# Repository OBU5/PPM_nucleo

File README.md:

# Proton precession magnetometer

Official repository for Proton precession magnetometer
In this repository are HW and SW files for the diploma thesis that is about designing, constrocting of proton precession magnetometer and analysis of its signal.
The aim is to construct PPM device that will be used for the earth’s magnetic field measurement

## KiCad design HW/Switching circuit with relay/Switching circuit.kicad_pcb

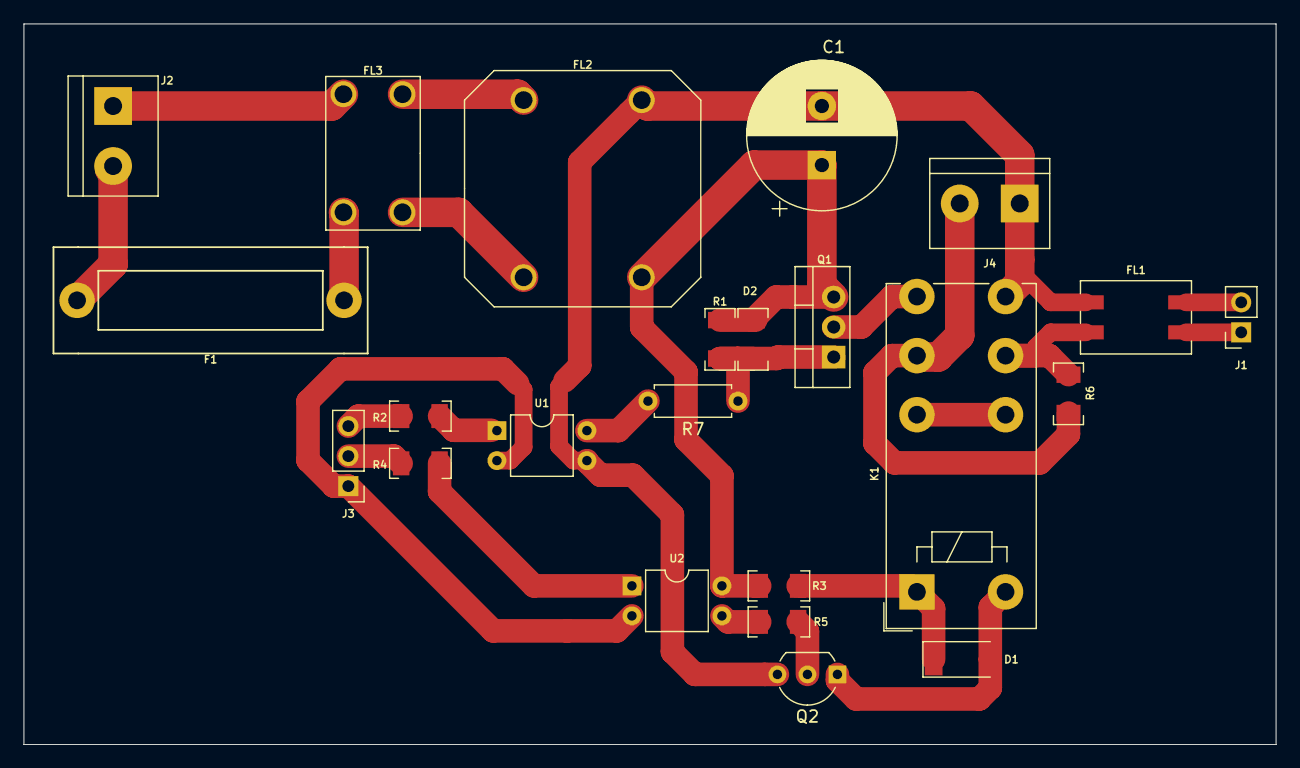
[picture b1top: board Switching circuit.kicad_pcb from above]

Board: 2 copper layers, 106.0 x 61.0 mm, 23 parts (0 on the bottom side), 24 nets.

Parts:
C1: CP; CP_Radial_D12.5mm_P5.00mm
D1: D; D_MELF
D2: 15V; R1206
F1: Fuse; Fuse_Holder-PTF15
FL1: Filter; WE-SL2
FL2: Filter; Choke1
FL3: Filter; Choke2
J1: Signal; PinSocket_1x02_P2.54mm_Vertical
J2: Power; TerminalBlock_2pin_Pitch5.08mm
J3: MCU; PinHeader_1x03_P2.54mm_Vertical
J4: PPM_sensor; TerminalBlock_2pin_Pitch5.08mm
K1: FINDER-41.52; Relay_DPDT_Finder_40.52
Q1: IRF9640; TO-220-3_Vertical
Q2: BC547; TO-92_Inline_Wide
R1: 2k2; R1206
R2, R4: 470; R1206
R3: 0; R1206
R5: 4k7; R1206
R6: 10k; R1206
R7: 1k; R_Axial_DIN0207_L6.3mm_D2.5mm_P7.62mm_Horizontal
U1, U2: LTV-817; DIP-4_W7.62mm

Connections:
+12V: C1.1, D2.1, FL2.3, Q1.3, R1.1, R3.1, U2.4
FET: J3.3, R2.2
GNDA: C1.2, FL1.1, FL2.4, J4.1, K1.24, Q2.3, U1.3
GNDD: J3.1, U1.2, U2.2
unnamed: D1.1, K1.A1, R3.2
unnamed: D1.2, K1.A2, Q2.1
unnamed: D2.2, Q1.1, R1.2, R7.1
unnamed: F1.1, FL3.2
unnamed: F1.2, J2.2
unnamed: FL1.3, J1.1
unnamed: FL1.4, J1.2
unnamed: FL2.1, FL3.4
unnamed: FL2.2, FL3.3
unnamed: FL3.1, J2.1
unnamed: J4.2, K1.11, R6.2
unnamed: K1.12, K1.22
unnamed: K1.14, Q1.2
unnamed: Q2.2, R5.2
unnamed: R2.1, U1.1
unnamed: R4.1, U2.1
unnamed: R5.1, U2.3
unnamed: R7.2, U1.4
Relay: J3.2, R4.2
Sig_out: FL1.2, K1.21, R6.1

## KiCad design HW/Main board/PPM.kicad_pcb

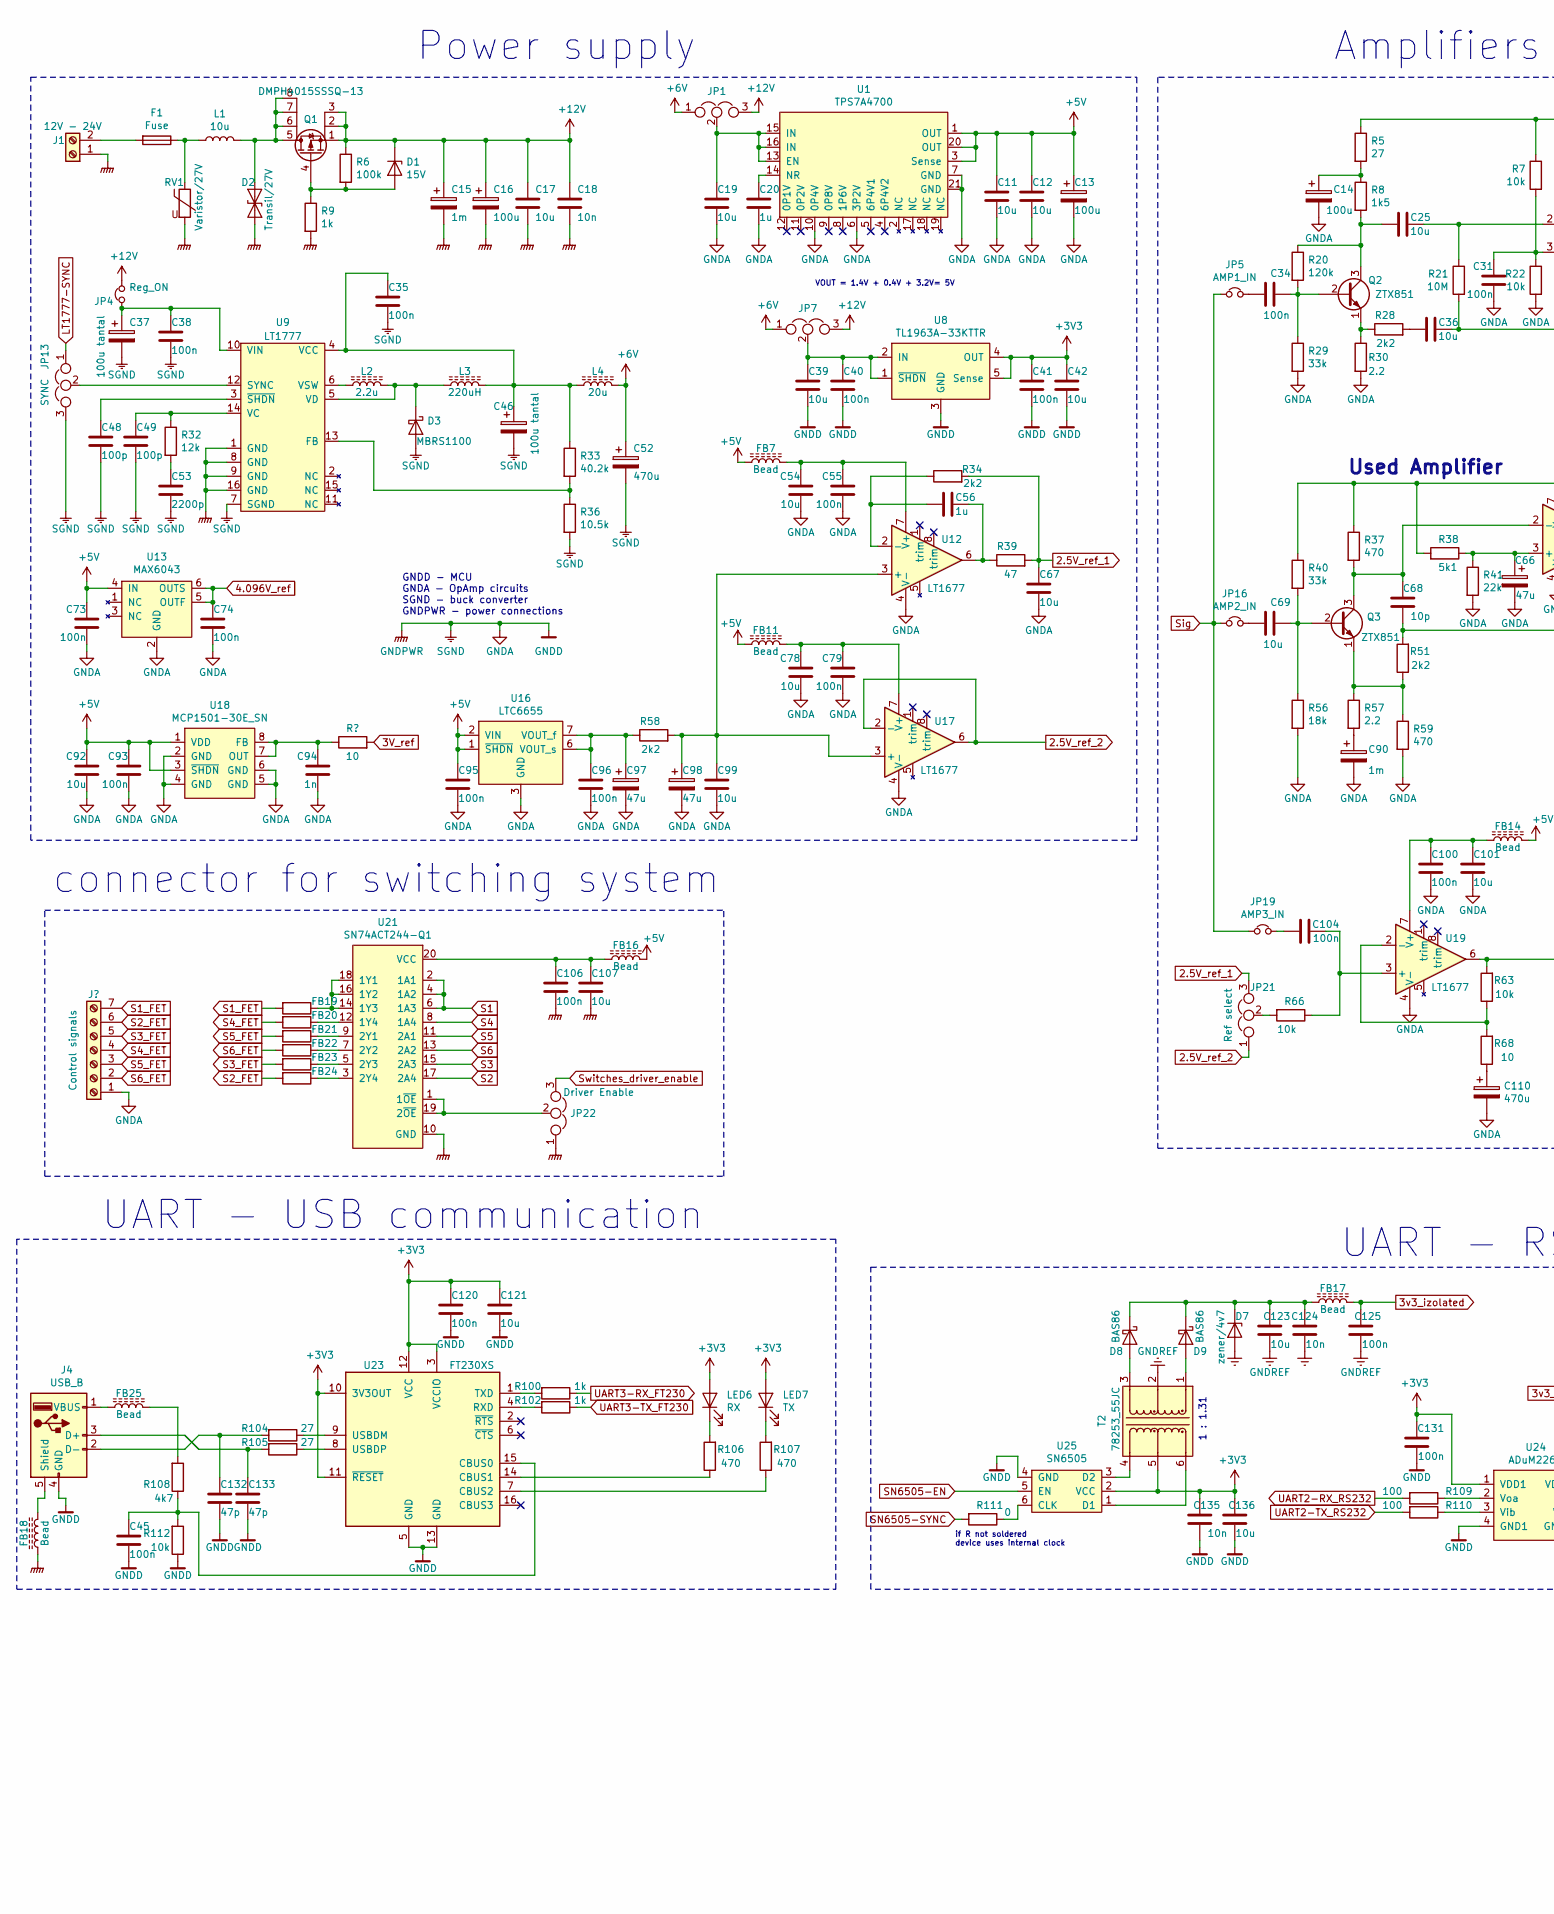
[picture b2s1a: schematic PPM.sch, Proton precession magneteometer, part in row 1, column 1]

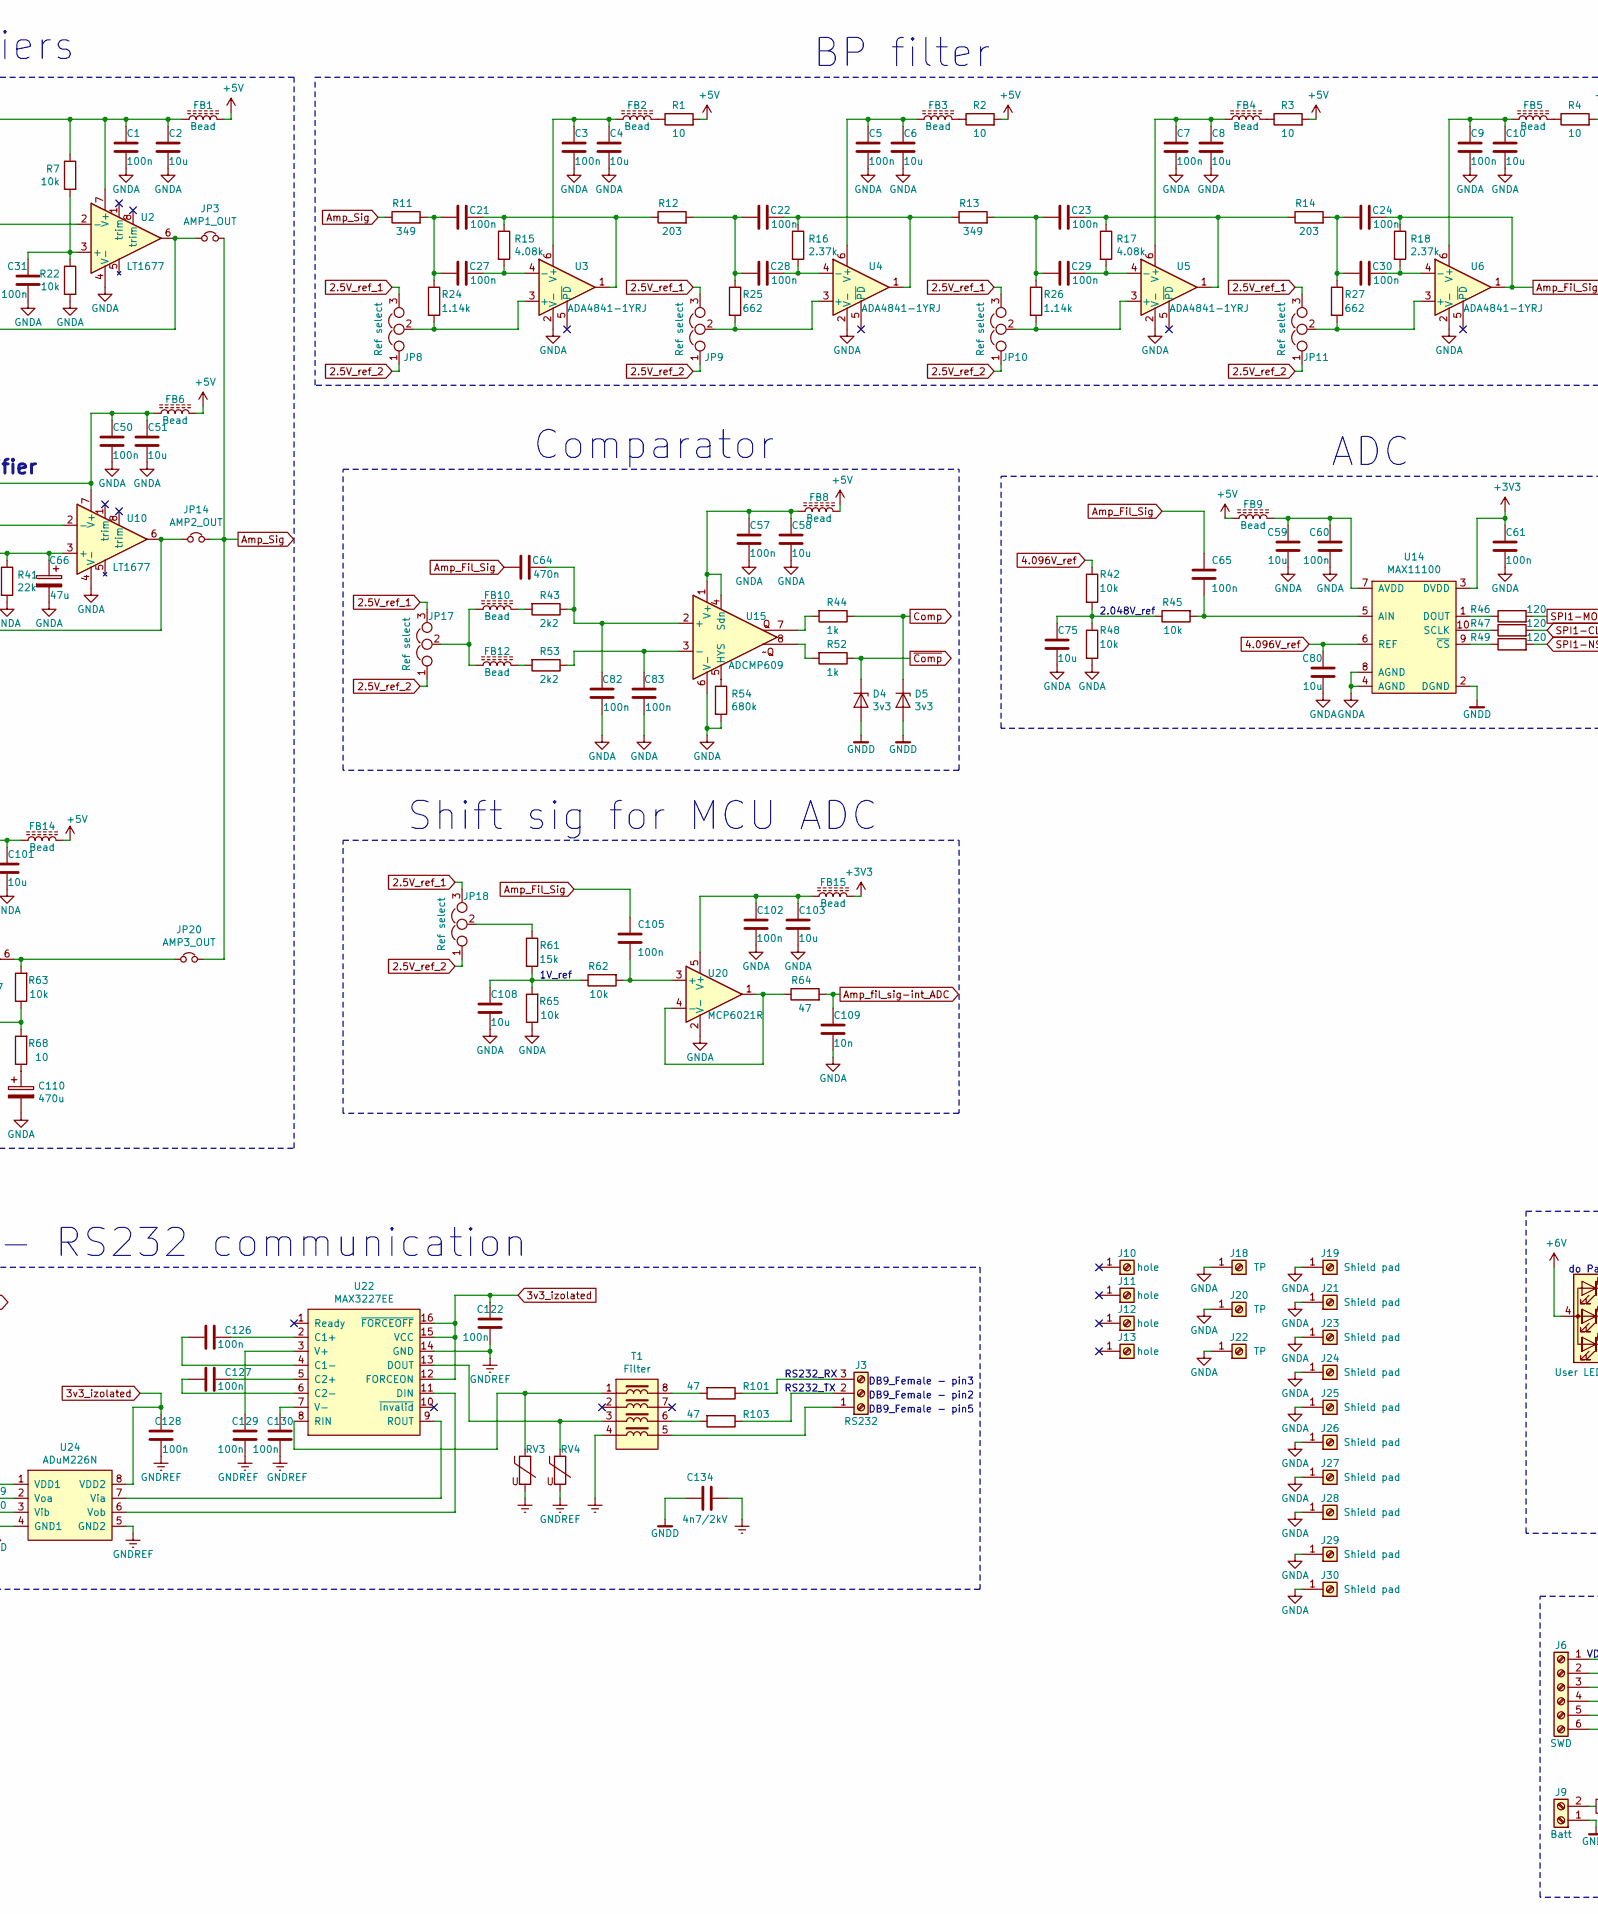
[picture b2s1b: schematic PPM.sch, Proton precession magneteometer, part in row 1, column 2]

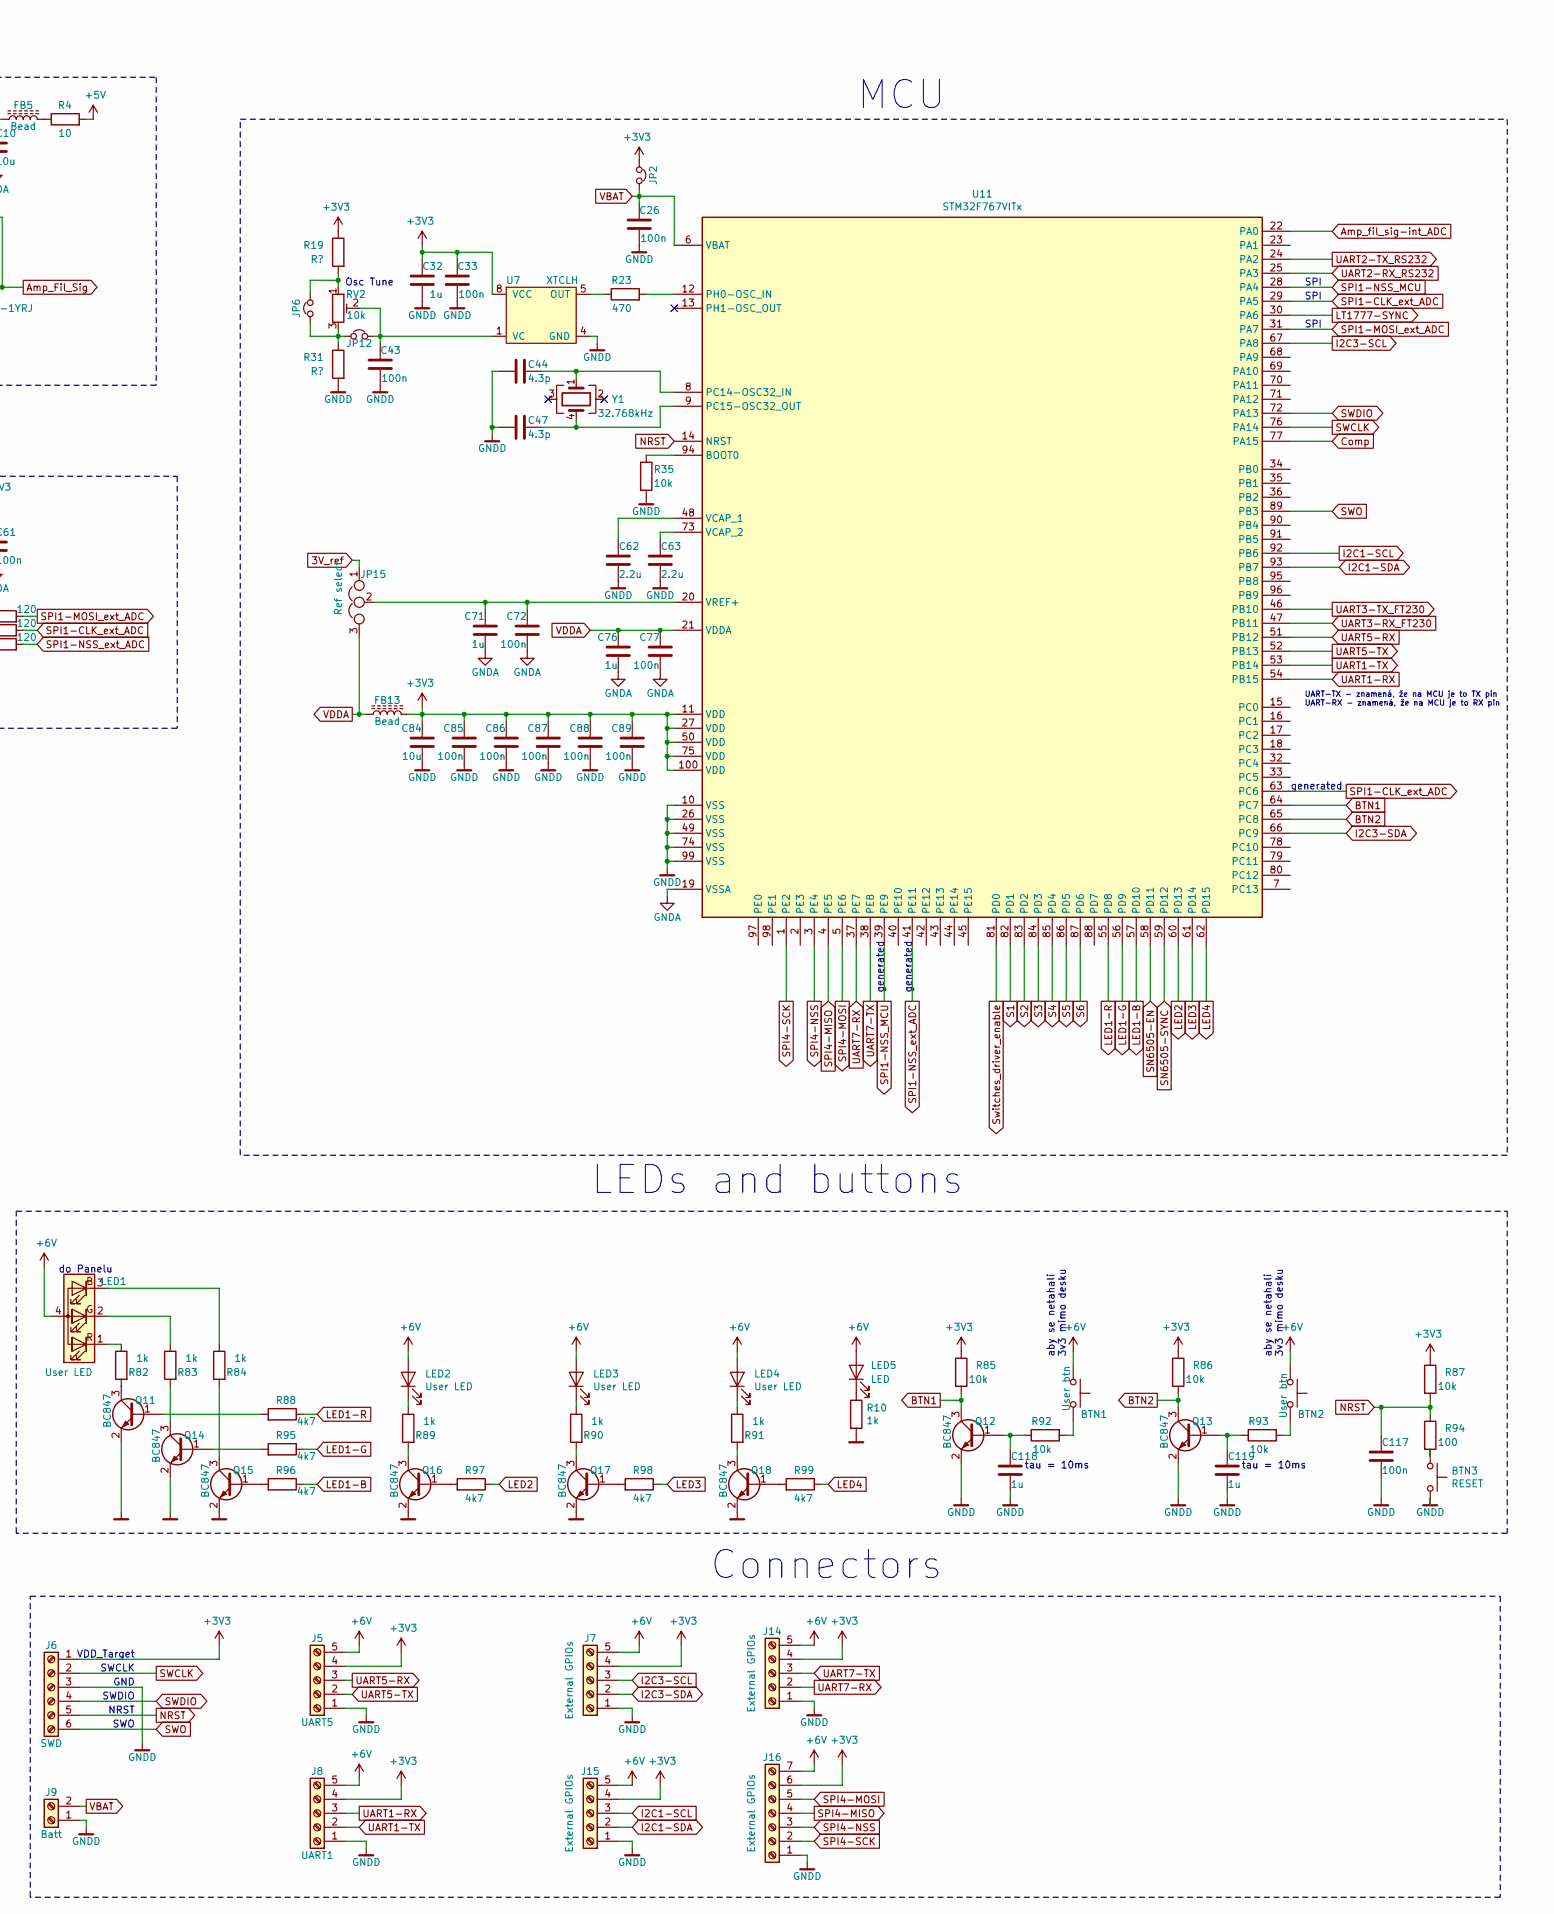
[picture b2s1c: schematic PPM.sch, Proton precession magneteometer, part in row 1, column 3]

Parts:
BTN1, BTN2: User btn; SW_PUSH_6mm
BTN3: RESET; SW_PUSH_6mm
C1, C3, C5, C7, C9, C26, C31, C33, C34, C35, C38, C40, C41, C43, C45, C50, C55, C57, C60, C61, C65, C72, C73, C74, C77, C79, C82, C83, C85, C86, C87, C88, C89, C93, C95, C96, C100, C102, C104, C105, C106, C117, C120, C122, C125, C126, C127, C128, C129, C130, C131: 100n; C0805
C2, C4, C6, C8, C10, C11, C12, C17, C19, C25, C36, C39, C42, C51, C54, C58, C59, C67, C69, C75, C78, C80, C84, C92, C99, C101, C103, C107, C108, C121, C123, C136: 10u; C1206
C13: 100u; CP_EIA-6032-28_Kemet-C
C14, C16: 100u; CP_Radial_D8.0mm_P3.50mm
C15: 1m; CP_Radial_D12.5mm_P5.00mm
C18, C109, C124, C135: 10n; C0805
C20, C32, C56, C71, C76, C118, C119: 1u; C0805
C21, C22, C23, C24, C27, C28, C29, C30: 100n; C_Rect_L7.2mm_W2.5mm_P5.00mm_FKS2_FKP2_MKS2_MKP2
C37: 100u tantal; CP_EIA-7343-20_Kemet-V
C44, C47: 4.3p; C0805
C46: 100u tantal; CP_EIA-6032-28_Kemet-C
C48, C49: 100p; C0805
C52: 470u; CP_Radial_D10.0mm_P5.00mm
C53: 2200p; C0805
C62, C63: 2.2u; C1206
C64: 470n; C0805
C66, C97, C98: 47u; CP_EIA-6032-28_Kemet-C
C68: 10p; C0805
C90: 1m; CP_Radial_D10.0mm_P5.00mm
C94: 1n; C0805
C110: 470u; CP_Radial_D8.0mm_P3.50mm
C132, C133: 47p; C0805
C134: 4n7/2kV; C1210
D1: 15V; D_SOD-123
D2: Transil/27V; D_SMC
D3: MBRS1100; D_SMB
D4, D5: 3v3; D_SOD-123
D7: zener/4v7; D_SOD-123
D8, D9: BAS86; D_MiniMELF
F1: Fuse; Fuse_Holder-PTF15
FB1, FB2, FB3, FB4, FB5, FB6, FB7, FB8, FB9, FB10, FB11, FB12, FB13, FB14, FB15, FB16, FB17, FB18, FB25: Bead; R0805
FB19, FB20, FB21, FB22, FB23, FB24: bead; R0805
J1: 12V - 24V; TerminalBlock_2pin_Pitch5.08mm
J3: RS232; PinHeader_1x03_P2.54mm_Vertical
J4: USB_B; USB_B_OST_USB-B1HSxx_Horizontal
J5: UART5; PinHeader_1x05_P2.54mm_Vertical
J6: SWD; PinHeader_1x06_P2.54mm_Vertical
J7, J14, J15: External GPIOs; PinHeader_1x05_P2.54mm_Vertical
J8: UART1; PinHeader_1x05_P2.54mm_Vertical
J9: Batt; PinHeader_1x02_P2.54mm_Vertical
J10, J11, J12, J13: hole; Screwh_hole-3.5mm
J16: External GPIOs; PinHeader_1x07_P2.54mm_Vertical
J18, J20, J22: TP; PinHeader_1x01_P2.54mm_Vertical
J19, J21, J23, J24, J25, J26, J27, J28, J29, J30: Shield pad; TestPoint
JP1: LDO-5V_supply; Jumper-3pin-P2.54+SMD
JP2, JP6, JP12: no osc tune; Jumper-2pin-P2.54+SMD
JP3: AMP1_OUT; Jumper-2pin-P2.54+SMD
JP4: Reg_ON; Jumper-2pin-P2.54+SMD
JP5: AMP1_IN; Jumper-2pin-P2.54+SMD
JP7: LDO-3V3_supply; Jumper-3pin-P2.54+SMD
JP8, JP9, JP10, JP11, JP15, JP17, JP18, JP21: Ref select; Jumper-3pin-P2.54+SMD
JP13: SYNC; Jumper-3pin-P2.54+SMD
JP14: AMP2_OUT; Jumper-2pin-P2.54+SMD
JP16: AMP2_IN; Jumper-2pin-P2.54+SMD
JP19: AMP3_IN; Jumper-2pin-P2.54+SMD
JP20: AMP3_OUT; Jumper-2pin-P2.54+SMD
JP22: Driver Enable; Jumper-3pin-P2.54+SMD
L1: 10u; Inductor_SRR1208
L2: 2.2u; Inductor_SRR0604
L3: 220uH; Inductor_12x12mm
L4: 20u; Inductor_SRR1208
LED1: User LED; PinHeader_1x04_P2.54mm_Vertical
LED2, LED3, LED4: User LED; LED-THT-3.0mm
LED5: LED; LED-THT-3.0mm
LED6: RX; LED-THT-3.0mm
LED7: TX; LED-THT-3.0mm
Q1: DMPH4015SSSQ-13; SOIC-8_3.9x4.9mm_P1.27mm
Q2, Q3: ZTX851; TO-92L_Inline
Q11, Q12, Q13, Q14, Q15, Q16, Q17, Q18: BC847; SOT-23
R1, R2, R3, R4, R68: 10; R0805
R5: 27; R1206
R6: 100k; R0805
R7, R22, R35, R42, R45, R48, R62, R63, R65, R66, R85, R86, R87, R92, R93, R112: 10k; R0805
R8: 1k5; R0805
R9, R10, R44, R52, R82, R83, R84, R89, R90, R91, R100, R102: 1k; R0805
R11, R13: 349; R0805
R12, R14: 203; R0805
R15, R17: 4.08k; R0805
R16, R18: 2.37k; R0805
R19, R31: R?; R0805
R20: 120k; R0805
R21: 10M; R0805
R23, R106, R107: 470; R0805
R24, R26: 1.14k; R0805
R25, R27: 662; R0805
R28, R34, R43, R51, R53, R58: 2k2; R0805
R29, R40: 33k; R0805
R30, R57: 2.2; R1206
R32: 12k; R0805
R33: 40.2k; R0805
R36: 10.5k; R0805
R37, R59: 470; R1206
R38: 5k1; R0805
R39, R64, R101, R103: 47; R0805
R41: 22k; R0805
R46, R47, R49: 120; R0805
R54: 680k; R0805
R56: 18k; R0805
R61: 15k; R0805
R88, R95, R96, R97, R98, R99, R108: 4k7; R0805
R94, R109, R110: 100; R0805
R104, R105: 27; R0805
R111: 0; R0805
RV1: Varistor/27V; B72210S0170K101
RV2: 10k; Potentiometer_Piher_PT-10-V10_Vertical_Hole
RV3, RV4: Varistor; SOT-23
T1: Filter; B82792C2
T2: 78253_55JC
U1: TPS7A4700; QFN-20-1EP_5x5mm_P0.65mm_EP3.35x3.35mm
U2, U10, U12, U17, U19: LT1677; SO-8_3.9x4.9mm_P1.27mm
U3, U4, U5, U6: ADA4841-1YRJ; SOT-23-6
U7: XTCLH
U8: TL1963A-33KTTR; TO-263-5_TabPin3
U9: LT1777; STC_SOP-16_3.9x9.9mm_P1.27mm
U11: STM32F767VITx; LQFP-100_14x14mm_P0.5mm
U13: MAX6043; SOT-23-6
U14: MAX11100; UMAX-10
U15: ADCMP609; MSOP-8_3x3mm_P0.65mm
U16: LTC6655; MSOP-8_3x3mm_P0.65mm
U18: MCP1501-30E_SN; SOIC-8_3.9x4.9mm_P1.27mm
U20: MCP6021R; SOT-23-5
U21: SN74ACT244-Q1; TSSOP-20_4.4x6.5mm_P0.65mm
U22: MAX3227EE; SSOP-16_5.3x6.2mm_P0.65mm
U23: FT230XS; SSOP-16_3.9x4.9mm_P0.635mm
U24: ADuM226N; SOIC-8_7.5x5.85mm_P1.27mm
U25: SN6505; SOT-23-6
Y1: 32.768kHz; Crystal-ABS25

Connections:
2.5V_ref_1: C67.1, JP8.3, JP9.3, JP10.3, JP11.3, JP17.3, JP18.3, JP21.3, R34.2, R39.2
3v3_izolated: C122.2, C125.2, C128.2, FB17.2, U22.12 (FORCEON), U22.15 (VCC), U22.16 (~FORCEOFF), U24.8 (VDD2)
4.096V_ref: C74.1, C80.1, R42.1, U13.5 (OUTF), U13.6 (OUTS), U14.6 (REF)
+3V3: C32.1, C33.1, C41.1, C42.1, C61.1, C84.1, C85.1, C86.1, C87.1, C88.1, C89.1, C120.1, C121.1, C131.2, C135.2, C136.2, FB13.1, FB15.2, J5.4, J6.1, J7.4, J8.4, J14.4, J15.4, J16.6, JP2.1, LED6.2 (A), LED7.2 (A), R19.1, R85.1, R86.1, R87.1, T2.5, U7.8 (VCC), U8.4 (OUT), U8.5 (Sense), U11.11 (VDD), U11.27 (VDD), U11.50 (VDD), U11.75 (VDD), U11.100 (VDD), U14.3 (DVDD), U23.3 (VCCIO), U23.10 (3V3OUT), U23.11 (~RESET), U23.12 (VCC), U24.1 (VDD1), U25.2 (VCC)
+5V: C11.1, C12.1, C13.1, C73.1, C92.1, C93.1, C95.1, FB1.2, FB6.2, FB7.2, FB8.2, FB9.2, FB11.2, FB14.2, FB16.2, R1.2, R2.2, R3.2, R4.2, U1.1 (OUT), U1.3 (Sense), U1.20 (OUT), U13.4 (IN), U16.1 (~SHDN), U16.2 (VIN), U18.1 (VDD), U18.3 (~SHDN)
+6V: BTN1.1, BTN2.1, C52.1, J5.5, J7.5, J8.5, J14.5, J15.5, J16.7, JP1.1, JP7.1, L4.2, LED1.4 (A), LED2.2 (A), LED3.2 (A), LED4.2 (A), LED5.2 (A)
+12V: C15.1, C16.1, C17.1, C18.1, D1.1 (K), JP1.3, JP4.1, JP7.3, Q1.1 (S), Q1.2 (S), Q1.3 (S), R6.1; also elsewhere on the board
Amp_Fil_Sig: C24.2, C64.1, C65.2, C105.2, R18.1, U6.1
Amp_Sig: JP3.2, JP14.2, JP20.1, R11.1
Amp_fil_sig-int_ADC: C109.1, R64.2, U11.22 (PA0)
BTN1: Q12.3 (C), R85.2, U11.64 (PC7)
BTN2: Q13.3 (C), R86.2, U11.65 (PC8)
Comp: D5.1 (K), R44.1, U11.77 (PA15)
GNDA: BTN3.2, C1.2, C2.2, C3.2, C4.2, C5.2, C6.2, C7.2, C8.2, C9.2, C10.2, C11.2, C12.2, C13.2, C14.2, C15.2, C16.2, C17.2, C18.2, C19.2, C20.2, C26.2, C31.2, C32.2, C33.2, C35.2, C37.2, C38.2, C39.2, C40.2, C41.2, C42.2, C43.2, C44.2, C45.2, C46.2, C47.2, C48.2, C49.2, C50.2, C51.2, C52.2, C53.2, C54.2, C55.2, C57.2, C58.2, C59.2, C60.2, C61.2, C62.2, C63.2, C66.2, C67.2, C71.2, C72.2, C73.2, C74.2, C75.1, C76.2, C77.2, C78.2, C79.2, C80.2, C82.1, C83.1, C84.2, C85.2, C86.2, C87.2, C88.2, C89.2, C90.2, C92.2, C93.2, C94.2, C95.2, C96.2, C97.2, C98.2, C99.2, C100.2, C101.2, C102.2, C103.2, C106.2, C107.2, C108.1, C109.2, C110.2, C117.2, C118.2, C119.2, C120.2, C121.2, C131.1, C132.2, C133.2, C134.1, C135.1, C136.1, D2.2 (A2), D3.2 (A), D4.2 (A), D5.2 (A), FB18.1, J1.1, J4.4 (GND), J5.1, J6.3, J7.1, J8.1, J9.1, J14.1, J15.1, J16.1, J18.1, J19.1, J20.1, J21.1, J22.1, J23.1, J24.1, J25.1, J26.1, J27.1, J28.1, J29.1, J30.1, JP13.3, JP22.1, Q11.2 (E), Q12.2 (E), Q13.2 (E), Q14.2 (E), Q15.2 (E), Q16.2 (E), Q17.2 (E), Q18.2 (E), R9.2, R10.2, R22.2, R29.2, R30.2, R31.2, R35.2, R36.2, R41.2, R48.2, R54.2, R56.2, R59.2, R65.1, R112.1, RV1.2, U1.6 (3P2V), U1.7 (GND), U1.10 (0P4V), U1.21 (GND), U2.4 (V-), U3.2 (V-), U4.2 (V-), U5.2 (V-), U6.2 (V-), U7.4 (GND), U8.3 (GND), U9.1 (GND), U9.7 (SGND), U9.8 (GND), U9.9 (GND), U9.16 (GND), U10.4 (V-), U11.10 (VSS), U11.19 (VSSA), U11.26 (VSS), U11.49 (VSS), U11.74 (VSS), U11.99 (VSS), U12.4 (V-), U13.2 (GND), U14.2 (DGND), U14.4 (AGND), U14.8 (AGND), U15.6 (V-), U16.3 (GND), U16.4 (GND), U16.5 (GND), U16.8 (GND), U17.4 (V-), U18.2 (GND), U18.4 (GND), U18.5 (GND), U18.6 (GND), U19.4 (V-), U20.2 (V-), U21.10 (GND), U23.5 (GND), U23.13 (GND), U24.4 (GND1), U25.4 (GND); also elsewhere on the board
GNDREF: C122.1, C123.1, C124.1, C125.1, C128.1, C129.1, C130.1, C134.2, D7.2 (A), RV3.2, RV4.2, T1.4, T2.2, U22.14 (GND), U24.5 (GND2)
I2C1-SCL: J15.3, U11.92 (PB6)
I2C1-SDA: J15.2, U11.93 (PB7)
I2C3-SCL: J7.3, U11.67 (PA8)
I2C3-SDA: J7.2, U11.66 (PC9)
LED1-B: R96.1, U11.57 (PD10)
LED1-G: R95.1, U11.56 (PD9)
LED1-R: R88.1, U11.55 (PD8)
LED2: R97.1, U11.60 (PD13)
LED3: R98.1, U11.61 (PD14)
LED4: R99.1, U11.62 (PD15)
LT1777-SYNC: JP13.1, U11.30 (PA6)
NRST: C117.1, J6.5, R87.2, R94.1, U11.14 (NRST)
unnamed: BTN1.2, R92.2
unnamed: BTN2.2, R93.2
unnamed: BTN3.1, R94.2
unnamed: C1.1, C2.1, FB1.1, R5.1, R7.1, U2.7 (V+)
unnamed: C3.1, C4.1, FB2.1, U3.6 (V+)
unnamed: C5.1, C6.1, FB3.1, U4.6 (V+)
unnamed: C7.1, C8.1, FB4.1, U5.6 (V+)
unnamed: C9.1, C10.1, FB5.1, U6.6 (V+)
unnamed: C14.1, R5.2, R8.1
unnamed: C19.1, JP1.2, U1.13 (EN), U1.15 (IN), U1.16 (IN)
unnamed: C20.1, U1.14 (NR)
unnamed: C21.1, C27.1, R11.2, R24.1
unnamed: C21.2, R12.1, R15.1, U3.1
unnamed: C22.1, C28.1, R12.2, R25.1
unnamed: C22.2, R13.1, R16.1, U4.1
unnamed: C23.1, C29.1, R13.2, R26.1
unnamed: C23.2, R14.1, R17.1, U5.1
unnamed: C24.1, C30.1, R14.2, R27.1
unnamed: C25.1, R21.1, U2.2 (-)
unnamed: C25.2, Q2.3 (C), R8.2, R20.1
unnamed: C27.2, R15.2, U3.4 (-)
unnamed: C28.2, R16.2, U4.4 (-)
unnamed: C29.2, R17.2, U5.4 (-)
unnamed: C30.2, R18.2, U6.4 (-)
unnamed: C31.1, R7.2, R22.1, U2.3 (+)
unnamed: C34.1, Q2.2 (B), R20.2, R29.1
unnamed: C34.2, JP5.1
unnamed: C35.1, C46.1, L3.2, L4.1, R33.1, U9.4 (VCC)
unnamed: C36.1, JP3.1, R21.2, U2.6
unnamed: C36.2, R28.2
unnamed: C37.1, C38.1, JP4.2, U9.10 (VIN)
unnamed: C39.1, C40.1, JP7.2, U8.1 (~SHDN), U8.2 (IN)
unnamed: C43.1, JP12.1, RV2.2, U7.1 (VC)
unnamed: C44.1, U11.8 (PC14-OSC32_IN), Y1.1
unnamed: C45.1, R108.1, R112.2, U23.15 (CBUS0)
unnamed: C47.1, U11.9 (PC15-OSC32_OUT), Y1.4
unnamed: C48.1, U9.3 (~SHDN)
unnamed: C49.1, R32.1, U9.14 (VC)
unnamed: C50.1, C51.1, FB6.1, R37.1, R38.2, R40.1, U10.7 (V+)
unnamed: C53.1, R32.2
unnamed: C54.1, C55.1, FB7.1, U12.7 (V+)
unnamed: C56.1, R39.1, U12.6
unnamed: C56.2, R34.1, U12.2 (-)
unnamed: C57.1, C58.1, FB8.1, U15.1 (V+), U15.4 (Sdn)
unnamed: C59.1, C60.1, FB9.1, U14.7 (AVDD)
unnamed: C62.1, U11.48 (VCAP_1)
unnamed: C63.1, U11.73 (VCAP_2)
unnamed: C64.2, C82.2, R43.1, U15.2 (+)
unnamed: C65.1, R45.2, U14.5 (AIN)
unnamed: C66.1, R38.1, R41.1, U10.3 (+)
unnamed: C68.2, Q3.3 (C), R37.2, U10.2 (-)
unnamed: C69.1, Q3.2 (B), R40.2, R56.1
unnamed: C69.2, JP16.2
unnamed: C71.1, C72.1, JP15.2, U11.20 (VREF+)
unnamed: C75.2, R42.2, R45.1, R48.1
unnamed: C78.1, C79.1, FB11.1, U17.7 (V+)
unnamed: C83.2, R53.1, U15.3 (-)
unnamed: C90.1, R57.2
unnamed: C96.1, C97.1, R58.1, U16.6 (VOUT_s), U16.7 (VOUT_f)
unnamed: C98.1, C99.1, R58.2, U12.3 (+), U17.3 (+)
unnamed: C100.1, C101.1, FB14.1, U19.7 (V+)
unnamed: C102.1, C103.1, FB15.1, U20.5 (V+)
unnamed: C104.1, JP19.2
unnamed: C104.2, R66.1, U19.3 (+)
unnamed: C105.1, R62.2, U20.3 (+)
unnamed: C106.1, C107.1, FB16.1, U21.20 (VCC)
unnamed: C108.2, R61.2, R62.1, R65.2
unnamed: C110.1, R68.1
unnamed: C118.1, Q12.1 (B), R92.1
unnamed: C119.1, Q13.1 (B), R93.1
unnamed: C123.2, C124.2, D7.1 (K), D8.1 (K), D9.1 (K), FB17.1
unnamed: C126.1, U22.2 (C1+)
unnamed: C126.2, U22.4 (C1-)
unnamed: C127.1, U22.5 (C2+)
unnamed: C127.2, U22.6 (C2-)
unnamed: C129.2, U22.3 (V+)
unnamed: C130.2, U22.7 (V-)
unnamed: C132.1, J4.2 (D-), R104.2
unnamed: C133.1, J4.3 (D+), R105.2
unnamed: D1.2 (A), Q1.4 (G), R6.2, R9.1
unnamed: D2.1 (A1), L1.2, Q1.5 (D), Q1.6 (D), Q1.7 (D), Q1.8 (D)
unnamed: D3.1 (K), L2.2, L3.1, U9.5 (VD)
unnamed: D8.2 (A), T2.3
unnamed: D9.2 (A), T2.1
unnamed: F1.1, L1.1, RV1.1
unnamed: F1.2, J1.2
unnamed: FB2.2, R1.1
unnamed: FB3.2, R2.1
unnamed: FB4.2, R3.1
unnamed: FB5.2, R4.1
unnamed: FB10.1, FB12.1, JP17.2
unnamed: FB10.2, R43.2
unnamed: FB12.2, R53.2
unnamed: FB18.2, J4.5 (Shield)
unnamed: FB19.1, U21.14 (1Y3), U21.16 (1Y2), U21.18 (1Y1)
unnamed: FB20.1, U21.12 (1Y4)
unnamed: FB21.1, U21.9 (2Y1)
unnamed: FB22.1, U21.7 (2Y2)
unnamed: FB23.1, U21.5 (2Y3)
unnamed: FB24.1, U21.3 (2Y4)
unnamed: FB25.1, J4.1 (VBUS)
unnamed: FB25.2, R108.2
unnamed: J3.1, T1.5
unnamed: J3.2, R103.1
unnamed: J3.3, R101.1
unnamed: JP6.1, R19.2, RV2.1
unnamed: JP8.2, R24.2, U3.3 (+)
unnamed: JP9.2, R25.2, U4.3 (+)
unnamed: JP10.2, R26.2, U5.3 (+)
unnamed: JP11.2, R27.2, U6.3 (+)
unnamed: JP6.2, JP12.2, R31.1, RV2.3
unnamed: JP13.2, U9.12 (SYNC)
unnamed: JP18.2, R61.1
unnamed: JP20.2, R63.2, U19.6
unnamed: JP21.2, R66.2
unnamed: JP22.2, U21.1 (1~OE), U21.19 (2~OE)
unnamed: L2.1, U9.6 (VSW)
unnamed: LED1.1 (RK), R82.1
unnamed: LED1.2 (GK), R83.1
unnamed: LED1.3 (BK), R84.1
unnamed: LED2.1 (K), R89.1
unnamed: LED3.1 (K), R90.1
unnamed: LED4.1 (K), R91.1
unnamed: LED5.1 (K), R10.1
unnamed: LED6.1 (K), R106.2
unnamed: LED7.1 (K), R107.2
unnamed: Q2.1 (E), R28.1, R30.1
unnamed: Q3.1 (E), R51.1, R57.1, R59.1
unnamed: Q11.1 (B), R88.2
unnamed: Q11.3 (C), R82.2
unnamed: Q14.1 (B), R95.2
unnamed: Q14.3 (C), R83.2
unnamed: Q15.1 (B), R96.2
unnamed: Q15.3 (C), R84.2
unnamed: Q16.1 (B), R97.2
unnamed: Q16.3 (C), R89.2
unnamed: Q17.1 (B), R98.2
unnamed: Q17.3 (C), R90.2
unnamed: Q18.1 (B), R99.2
unnamed: Q18.3 (C), R91.2
unnamed: R23.1, U7.5 (OUT)
unnamed: R23.2, U11.12 (PH0-OSC_IN)
unnamed: R33.2, R36.1, U9.13 (FB)
unnamed: R35.1, U11.94 (BOOT0)
unnamed: R44.2, U15.7
unnamed: R46.1, U14.1 (DOUT)
unnamed: R47.1, U14.10 (SCLK)
unnamed: R49.1, U14.9 (~CS)
unnamed: R52.2, U15.8
unnamed: R54.1, U15.5 (HYS)
unnamed: R63.1, R68.2, U19.2 (-)
unnamed: R64.1, U20.1, U20.4 (-)
unnamed: R100.2, U23.1 (TXD)
unnamed: R101.2, T1.8
unnamed: R102.2, U23.4 (RXD)
unnamed: R103.2, T1.6
unnamed: R104.1, U23.9 (USBDM)
unnamed: R105.1, U23.8 (USBDP)
unnamed: R106.1, U23.14 (CBUS1)
unnamed: R107.1, U23.7 (CBUS2)
unnamed: R109.1, U24.2 (Voa)
unnamed: R110.1, U24.3 (Vib)
unnamed: R111.1, U25.6 (CLK)
unnamed: RV3.1, T1.1, U22.8 (RIN)
unnamed: RV4.1, T1.3, U22.13 (DOUT)
unnamed: T2.4, U25.3 (D2)
unnamed: T2.6, U25.1 (D1)
unnamed: U22.9 (ROUT), U24.7 (Via)
unnamed: U22.11 (DIN), U24.6 (Vob)
S1: U11.82 (PD1), U21.2 (1A1), U21.4 (1A2), U21.6 (1A3)
S1_FET: FB19.2; also elsewhere on the board
S2: U11.83 (PD2), U21.17 (2A4)
S2_FET: FB24.2; also elsewhere on the board
S3: U11.84 (PD3), U21.15 (2A3)
S3_FET: FB23.2; also elsewhere on the board
S4: U11.85 (PD4), U21.8 (1A4)
S4_FET: FB20.2; also elsewhere on the board
S5: U11.86 (PD5), U21.11 (2A1)
S5_FET: FB21.2; also elsewhere on the board
S6: U11.87 (PD6), U21.13 (2A2)
S6_FET: FB22.2; also elsewhere on the board
SN6505-EN: U11.58 (PD11), U25.5 (EN)
SN6505-SYNC: R111.2, U11.59 (PD12)
SPI1-CLK_ext_ADC: R47.2, U11.29 (PA5), U11.63 (PC6)
SPI1-MOSI_ext_ADC: R46.2, U11.31 (PA7)
SPI1-NSS_MCU: U11.28 (PA4), U11.39 (PE9)
SPI1-NSS_ext_ADC: R49.2, U11.41 (PE11)
SPI4-MISO: J16.4, U11.4 (PE5)
SPI4-MOSI: J16.5, U11.5 (PE6)
SPI4-NSS: J16.3, U11.3 (PE4)
SPI4-SCK: J16.2, U11.1 (PE2)
SWCLK: J6.2, U11.76 (PA14)
SWDIO: J6.4, U11.72 (PA13)
SWO: J6.6, U11.89 (PB3)
Sig: JP5.2, JP16.1, JP19.1; also elsewhere on the board
Switches_driver_enable: JP22.3, U11.81 (PD0)
UART1-RX: J8.3, U11.54 (PB15)
UART1-TX: J8.2, U11.53 (PB14)
UART2-RX_RS232: R109.2, U11.25 (PA3)
UART2-TX_RS232: R110.2, U11.24 (PA2)
UART3-RX_FT230: R100.1, U11.47 (PB11)
UART3-TX_FT230: R102.1, U11.46 (PB10)
UART5-RX: J5.3, U11.51 (PB12)
UART5-TX: J5.2, U11.52 (PB13)
UART7-RX: J14.2, U11.37 (PE7)
UART7-TX: J14.3, U11.38 (PE8)
VBAT: C26.1, J9.2, JP2.2, U11.6 (VBAT)
VDDA: C76.1, C77.1, FB13.2, JP15.3, U11.21 (VDDA)
~Comp: D4.1 (K), R52.1

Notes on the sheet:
GNDD - MCU GNDA - OpAmp circuits SGND - buck converter GNDPWR - power connections
Power supply
connector for switching system
UART - USB communication
ADC
BP filter
Amplifiers
Shift sig for MCU ADC
VOUT = 1.4V + 0.4V + 3.2V= 5V
1V_ref
1 : 1.31
UART - RS232 communication
RS232_RX
RS232_TX
2.048V_ref
VDD_Target
SWCLK
GND
SWDIO
NRST
SWO
if R not soldered device uses internal clock
generated
SPI
Comparator
MCU
Connectors
UART-TX - znamená, že na MCU je to TX pin UART-RX - znamená, že na MCU je to RX pin
Osc Tune
do Panelu
tau = 10ms
LEDs and buttons
aby se netahali 3v3 mimo desku
DB9_Female - pin2
DB9_Female - pin3
DB9_Female - pin5
Used Amplifier

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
